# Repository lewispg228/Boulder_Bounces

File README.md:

# Boulder Bounces
The Museum of Boulder exhibit designers have paired with SparkFun to create Boulder Bounces: a mashup of Simon Says on trampolines. With sounds and spot lights triggering for every jump in the room, the exhibit is a bouncy blast for all ages.

Also includes slightly different code for the "Mighty Mini" and "Hop & Hear".

For a more in depth written post about the design choices, challenges, and future developments please visit the Enginursday blog post here:

https://www.sparkfun.com/news/2696

Visit this website for more info and links to all the products used in this project:

https://www.sparkfun.com/boulderbounces

To learn more about the Museum of Boulder and buy tickets please visit their website here:

https://www.museumofboulder.org

SparkFun products used in this project:

[Arduino Pro Mini 328 - 5V/16MHz](https://www.sparkfun.com/products/11113)

[Ultrasonic Sensor - HC-SR04](https://www.sparkfun.com/products/13959)

[Tsunami Super WAV Trigger](https://www.sparkfun.com/products/13810)

[SparkFun Beefcake Relay Control Kit Ver. 2.0](https://www.sparkfun.com/products/13815)

[SparkFun Music Instrument Shield](https://www.sparkfun.com/products/10587)

[7-Segment Display - 6.5" (Red)](https://www.sparkfun.com/products/8530)

[SparkFun Large Digit Driver](https://www.sparkfun.com/products/13279)

[SparkFun Noisy Cricket Stereo Amplifier - 1.5W](https://www.sparkfun.com/products/14475)

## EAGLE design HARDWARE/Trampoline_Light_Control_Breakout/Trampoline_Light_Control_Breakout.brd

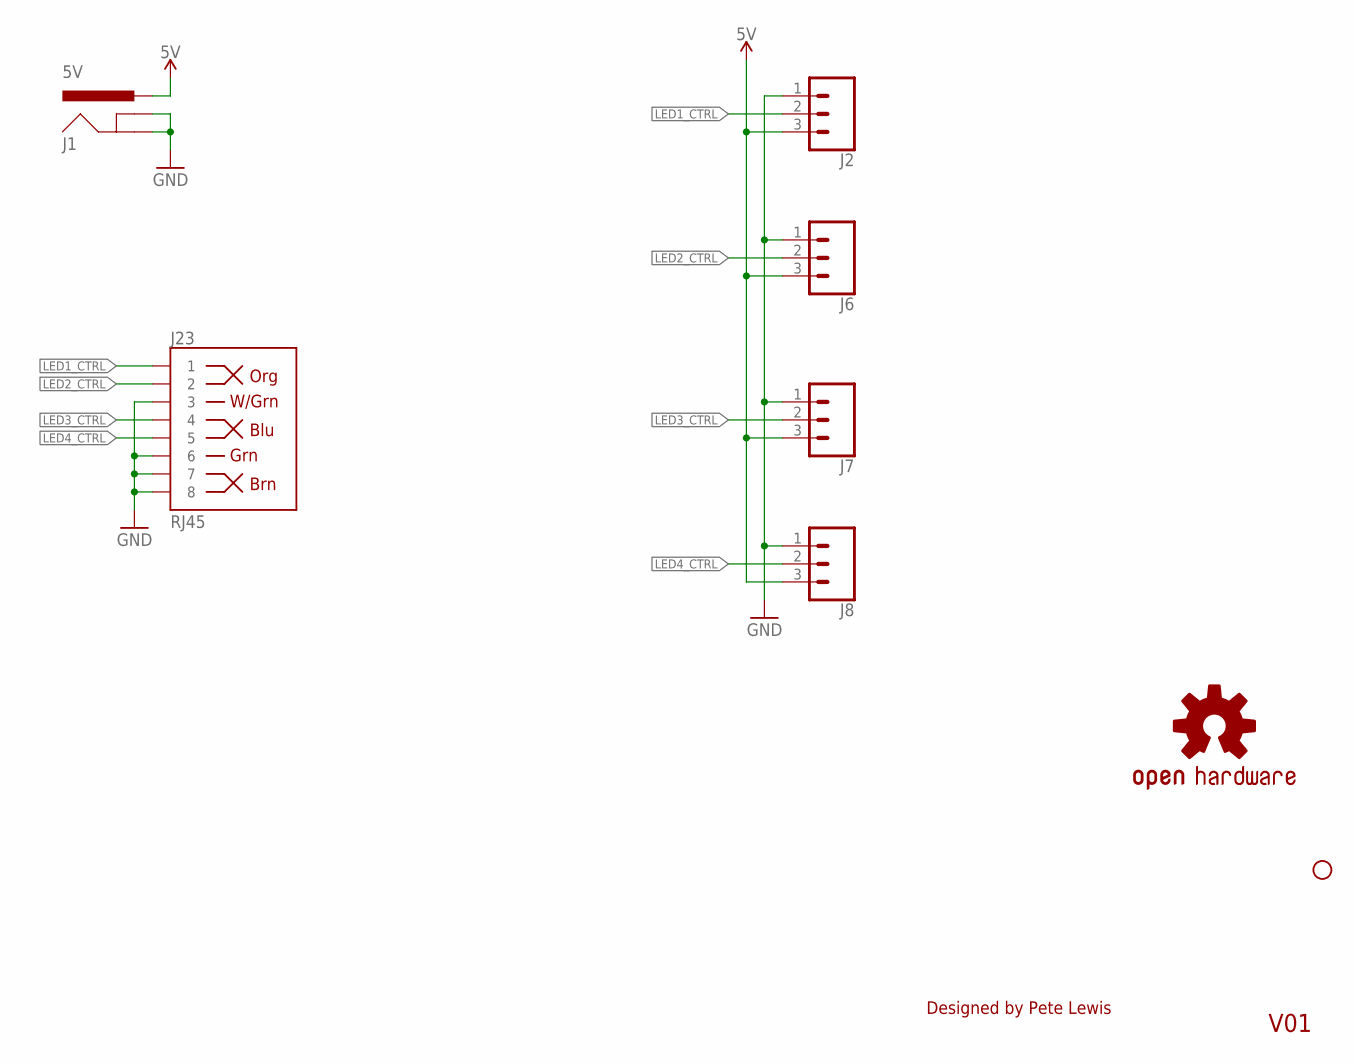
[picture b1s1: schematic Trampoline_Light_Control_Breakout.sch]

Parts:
J1: 5V; POWER_JACK_PTH_LOCK
J2, J6, J7, J8: CONN_03LONGPADS; 1X03_LONGPADS
J23: RJ45; RJ45-8
JP1: STAND-OFFTIGHTER; STAND-OFF-TIGHTER
LOGO2: OSHW-LOGOS; OSHW-LOGO-S

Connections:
GND: J1.GND, J1.GNDBREAK, J2.1, J6.1, J7.1, J8.1, J23.3, J23.6, J23.7, J23.8
LED1_CTRL: J2.2, J23.1
LED2_CTRL: J6.2, J23.2
LED3_CTRL: J7.2, J23.4
LED4_CTRL: J8.2, J23.5
VCC: J1.PWR, J2.3, J6.3, J7.3, J8.3

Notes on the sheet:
V01
Designed by Pete Lewis

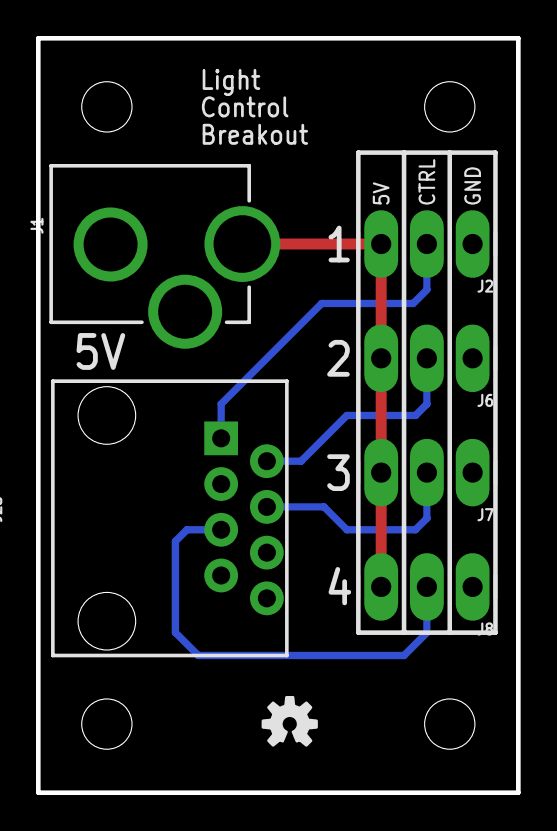
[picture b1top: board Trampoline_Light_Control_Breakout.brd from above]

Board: 2 copper layers, 26.7 x 41.9 mm, 11 parts (0 on the bottom side), 6 nets.

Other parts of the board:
JP2, JP3, JP7: STAND-OFFTIGHTER; STAND-OFF-TIGHTER

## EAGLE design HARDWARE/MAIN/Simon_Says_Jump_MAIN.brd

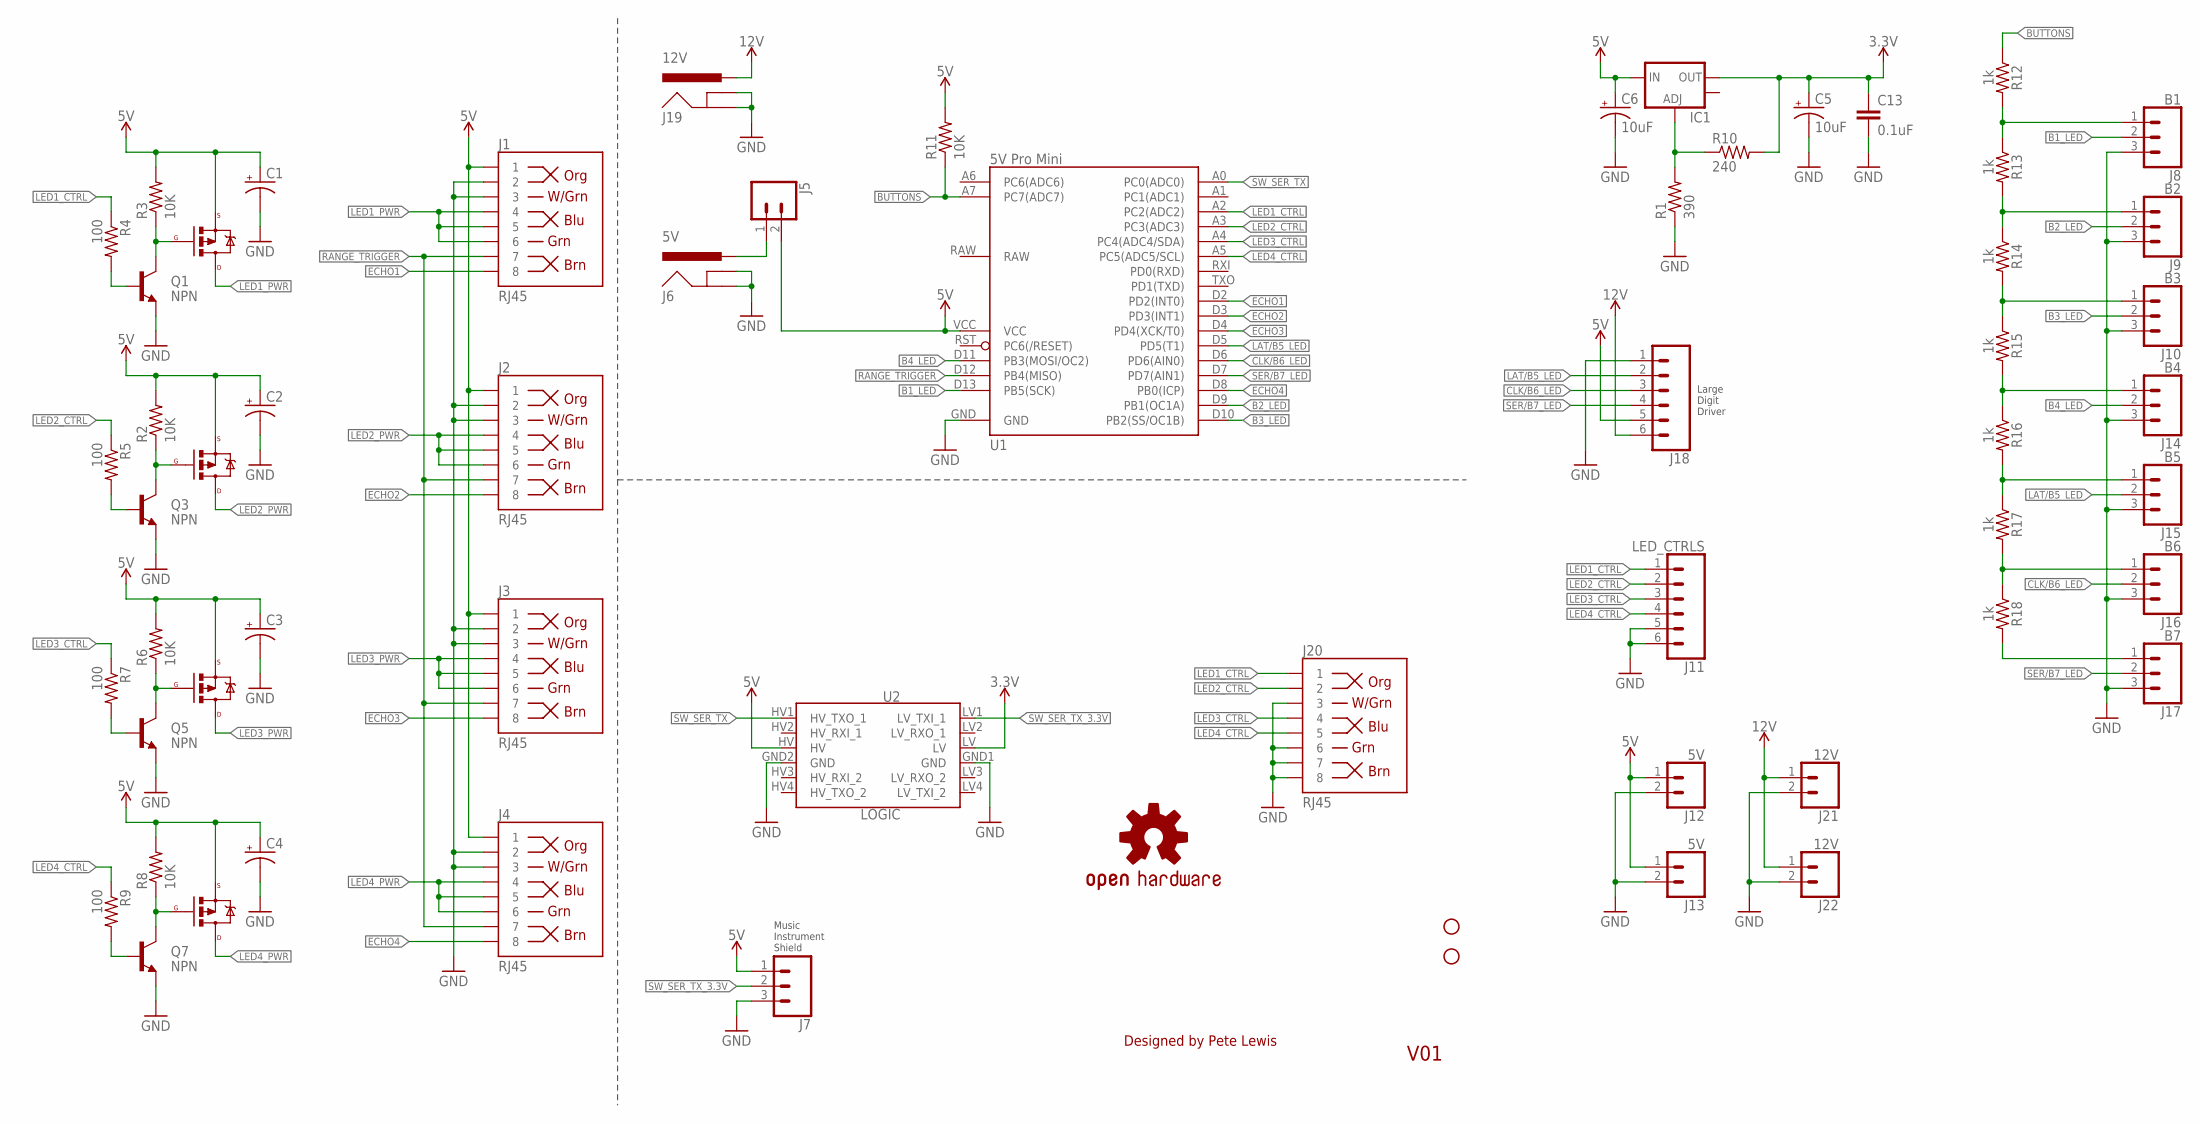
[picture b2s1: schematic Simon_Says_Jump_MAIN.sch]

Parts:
C1, C2, C3, C4: CAP_POLCPOL-RADIAL-10UF-25V-KIT; CPOL-RADIAL-10UF-25V-KIT
C5, C6: 10uF; EIA3216
C13: 0.1uF; 0603-CAP
IC1: V_REG_LM1117SOT223; SOT223
J1, J2, J3, J4, J20: RJ45; RJ45-8
J5: CONN_02PTH3; 1X02_LONGPADS
J6: 5V; POWER_JACK_PTH_LOCK
J7: CONN_03LONGPADS; 1X03_LONGPADS
J8: B1; 1X03_LONGPADS
J9: B2; 1X03_LONGPADS
J10: B3; 1X03_LONGPADS
J11: LED_CTRLS; 1X06_LONGPADS
J12, J13: 5V; 1X02_LONGPADS
J14: B4; 1X03_LONGPADS
J15: B5; 1X03_LONGPADS
J16: B6; 1X03_LONGPADS
J17: B7; 1X03_LONGPADS
J18: CONN_06LONGPADS; 1X06_LONGPADS
J19: 12V; POWER_JACK_PTH_LOCK
J21, J22: 12V; 1X02_LONGPADS
JP1, JP7: STAND-OFFTIGHTER; STAND-OFF-TIGHTER
LOGO1: OSHW-LOGOL; OSHW-LOGO-L
Q1, Q3, Q5, Q7: NPN; SOT23
Q2, Q4, Q6, Q8: P-Channel MOSFET; TO220V
R1: 390; 0603-RES
R2, R3, R6, R8, R11: 10K; 0603-RES
R4, R5, R7, R9: 100; 0603-RES
R10: 240; 0603-RES
R12, R13, R14, R15, R16, R17, R18: 1k; 0603
U1: 5V Pro Mini; ARDUINO_PRO_MINI-V13_DIP
U2: LOGIC; SPARKFUN_LOGIC_LEVEL_CONVERTER

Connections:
3.3V: C5.A (+), C13.1, IC1.2 (OUT), R10.2, U2.LV
5V: C1.1 (+), C2.1 (+), C3.1 (+), C4.1 (+), C6.A (+), IC1.3 (IN), J1.1, J2.1, J3.1, J4.1, J5.2, J7.1, J12.1, J13.1, J18.5, Q2.3 (S), Q4.3 (S), Q6.3 (S), Q8.3 (S), R2.2, R3.2, R6.2, R8.2, R11.2, U1.VCC, U2.HV
12V: J18.6, J19.PWR, J21.1, J22.1
B1_LED: J8.2, U1.D13 (PB5(SCK))
B2_LED: J9.2, U1.D9 (PB1(OC1A))
B3_LED: J10.2, U1.D10 (PB2(SS/OC1B))
B4_LED: J14.2, U1.D11 (PB3(MOSI/OC2))
BUTTONS: R11.1, R12.1, U1.A7 (PC7(ADC7))
CLK/B6_LED: J16.2, J18.3, U1.D6 (PD6(AIN0))
ECHO1: J1.8, U1.D2 (PD2(INT0))
ECHO2: J2.8, U1.D3 (PD3(INT1))
ECHO3: J3.8, U1.D4 (PD4(XCK/T0))
ECHO4: J4.8, U1.D8 (PB0(ICP))
GND: C1.2 (-), C2.2 (-), C3.2 (-), C4.2 (-), C5.C (-), C6.C (-), C13.2, J1.2, J1.3, J2.2, J2.3, J3.2, J3.3, J4.2, J4.3, J6.GND, J6.GNDBREAK, J7.3, J8.3, J9.3, J10.3, J11.5, J11.6, J12.2, J13.2, J14.3, J15.3, J16.3, J17.3, J18.1, J19.GND, J19.GNDBREAK, J20.3, J20.6, J20.7, J20.8, J21.2, J22.2, Q1.2 (E), Q3.2 (E), Q5.2 (E), Q7.2 (E), R1.1, U1.GND, U2.GND1 (GND), U2.GND2 (GND)
LAT/B5_LED: J15.2, J18.2, U1.D5 (PD5(T1))
LED1_CTRL: J11.1, J20.1, R4.1, U1.A2 (PC2(ADC2))
LED1_PWR: J1.4, J1.5, J1.6, Q2.2 (D)
LED2_CTRL: J11.2, J20.2, R5.1, U1.A3 (PC3(ADC3))
LED2_PWR: J2.4, J2.5, J2.6, Q4.2 (D)
LED3_CTRL: J11.3, J20.4, R7.1, U1.A4 (PC4(ADC4/SDA))
LED3_PWR: J3.4, J3.5, J3.6, Q6.2 (D)
LED4_CTRL: J11.4, J20.5, R9.1, U1.A5 (PC5(ADC5/SCL))
LED4_PWR: J4.4, J4.5, J4.6, Q8.2 (D)
unnamed: Q3.3 (C), Q4.1 (G), R2.1
unnamed: J8.1, R12.2, R13.1
unnamed: Q1.1 (B), R4.2
unnamed: J5.1, J6.PWR
unnamed: Q1.3 (C), Q2.1 (G), R3.1
unnamed: J9.1, R13.2, R14.1
unnamed: Q3.1 (B), R5.2
unnamed: Q5.3 (C), Q6.1 (G), R6.1
unnamed: Q5.1 (B), R7.2
unnamed: Q7.3 (C), Q8.1 (G), R8.1
unnamed: IC1.1 (ADJ), R1.2, R10.1
unnamed: Q7.1 (B), R9.2
unnamed: J10.1, R14.2, R15.1
unnamed: J14.1, R15.2, R16.1
unnamed: J15.1, R16.2, R17.1
unnamed: J16.1, R17.2, R18.1
unnamed: J17.1, R18.2
RANGE_TRIGGER: J1.7, J2.7, J3.7, J4.7, U1.D12 (PB4(MISO))
SER/B7_LED: J17.2, J18.4, U1.D7 (PD7(AIN1))
SW_SER_TX: U1.A0 (PC0(ADC0)), U2.HV1 (HV_TXO_1)
SW_SER_TX_3.3V: J7.2, U2.LV1 (LV_TXI_1)

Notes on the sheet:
V01
Designed by Pete Lewis
Music Instrument Shield
Large Digit Driver

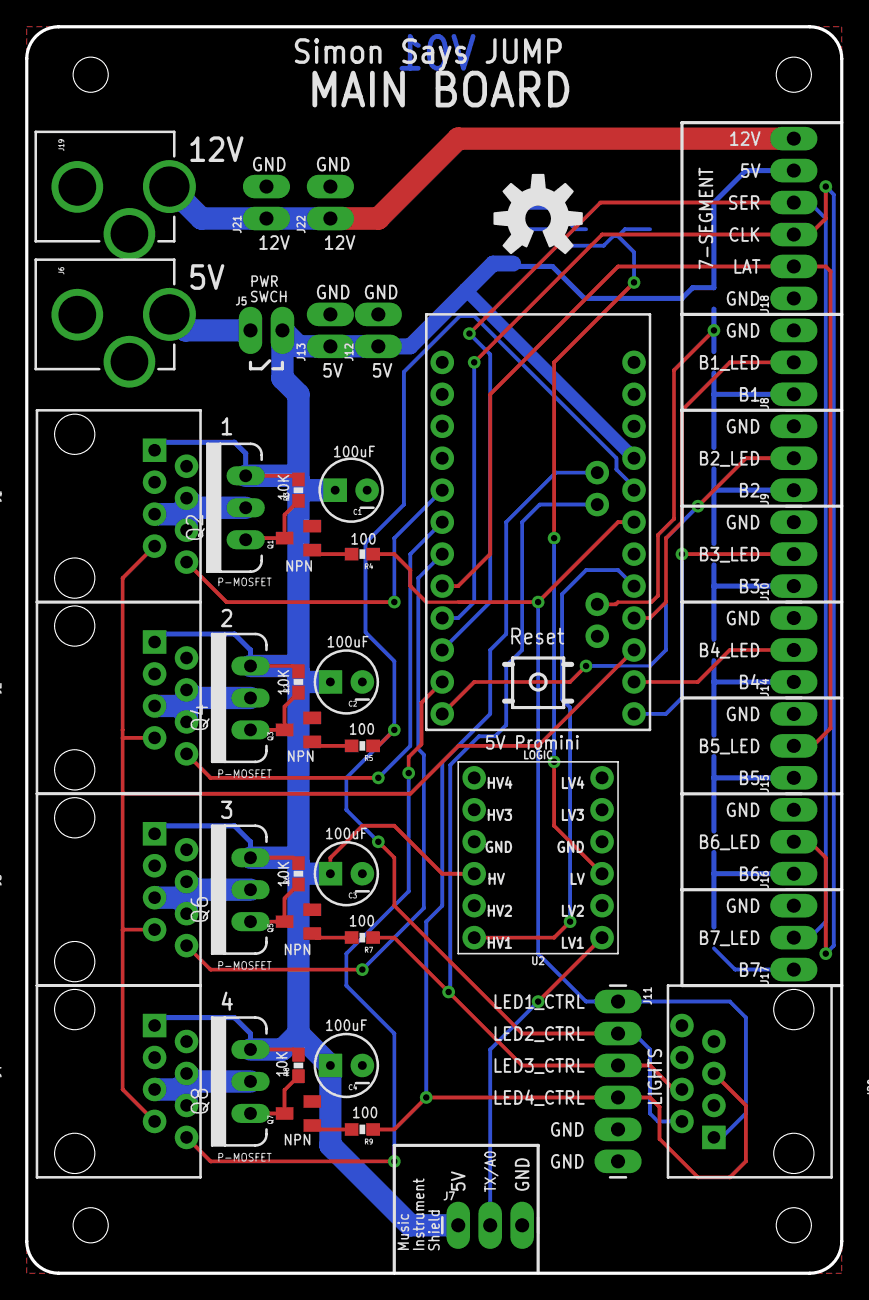
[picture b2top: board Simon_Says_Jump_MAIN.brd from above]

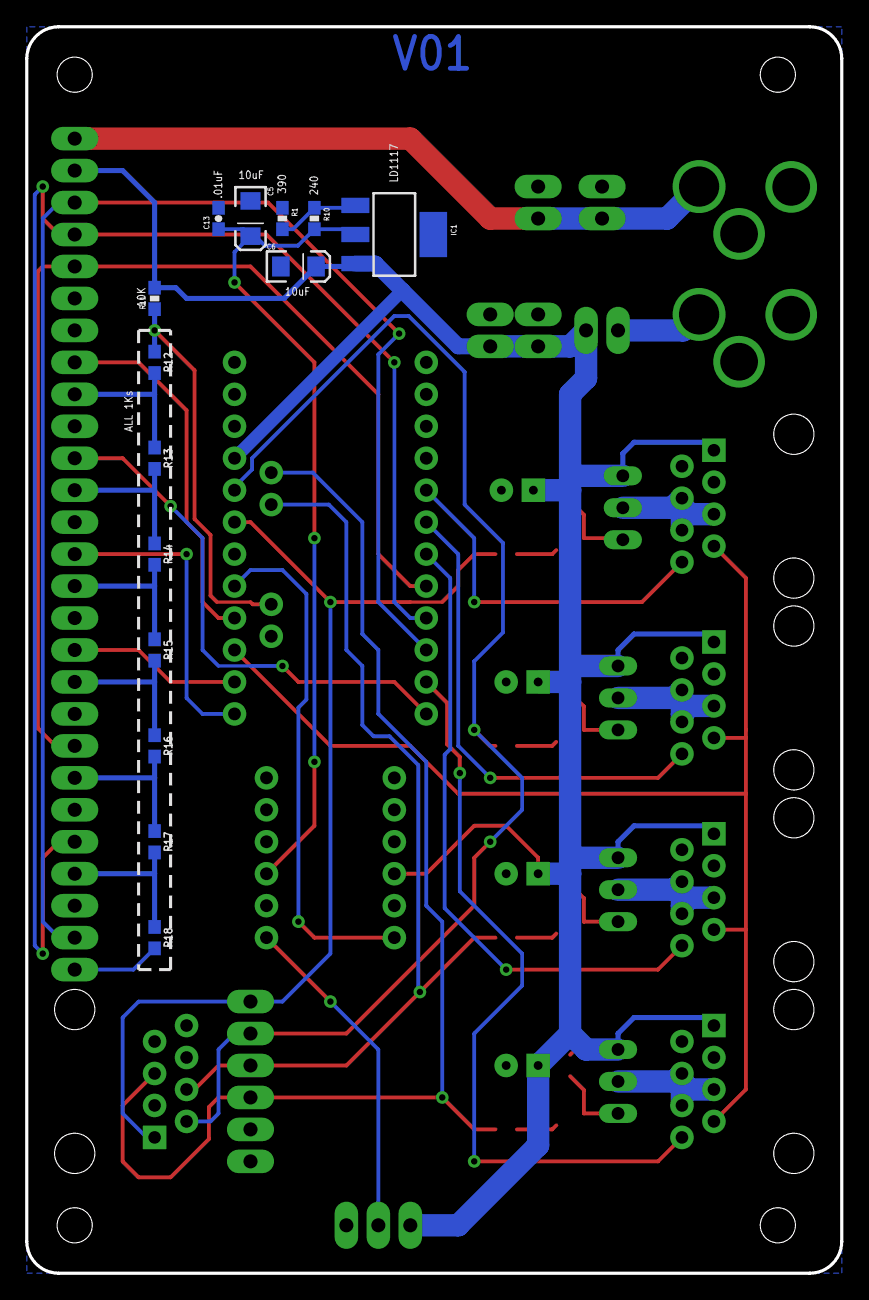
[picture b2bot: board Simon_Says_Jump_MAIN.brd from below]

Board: 2 copper layers, 64.8 x 99.1 mm, 63 parts (14 on the bottom side), 44 nets.

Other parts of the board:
JP2, JP3: STAND-OFFTIGHTER; STAND-OFF-TIGHTER

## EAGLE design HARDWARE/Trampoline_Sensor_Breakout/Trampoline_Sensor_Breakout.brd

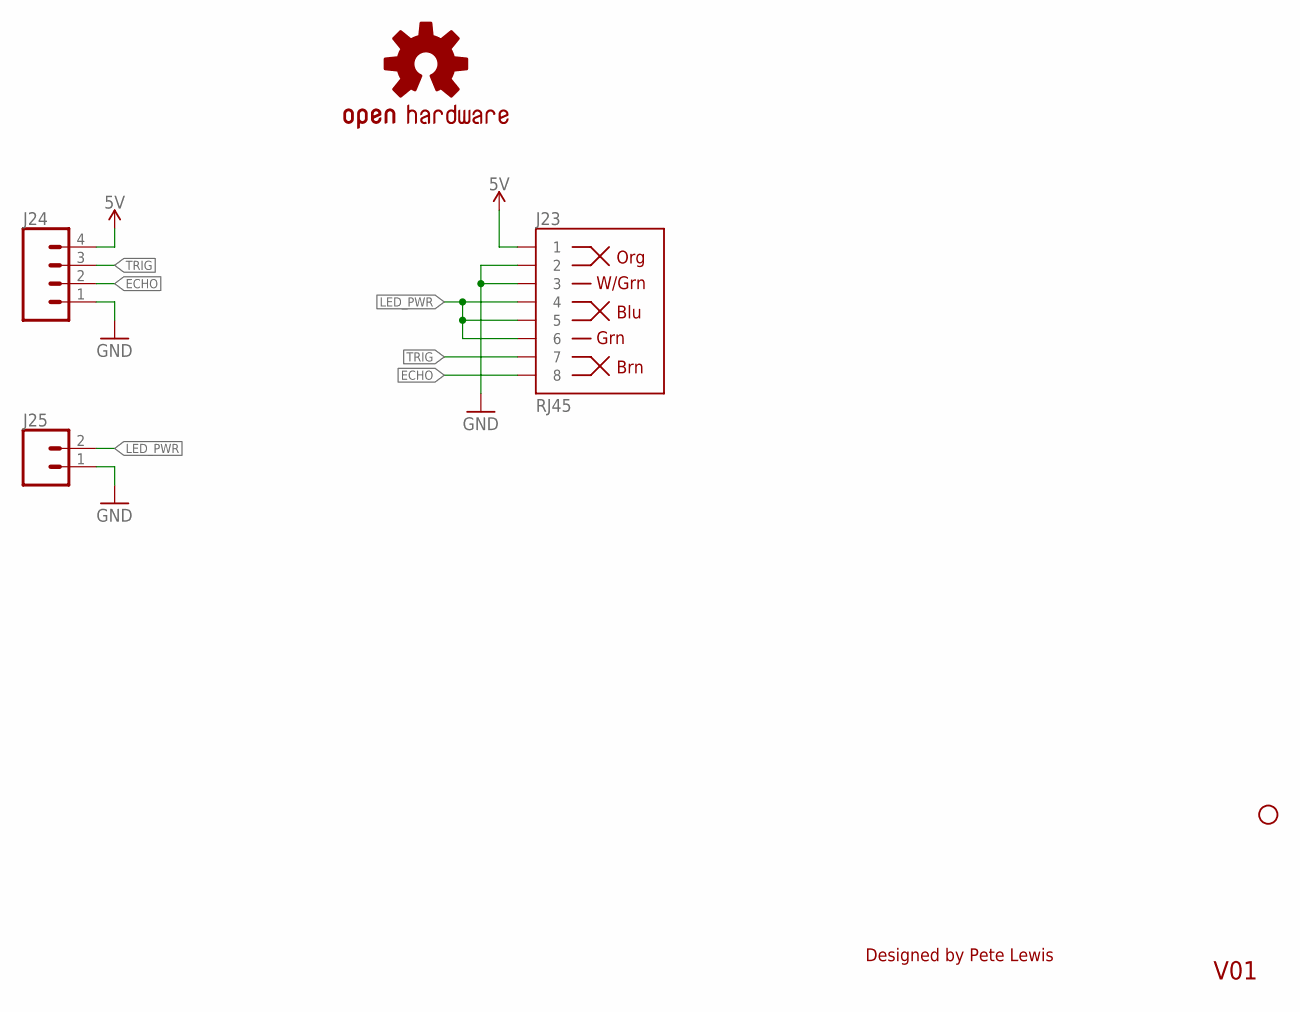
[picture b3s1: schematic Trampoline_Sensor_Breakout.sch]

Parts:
J23: RJ45; RJ45-8
J24: CONN_04LONGPADS; 1X04_LONGPADS
J25: CONN_02PTH3; 1X02_LONGPADS
JP8: STAND-OFFTIGHTER; STAND-OFF-TIGHTER
LOGO2: OSHW-LOGOS; OSHW-LOGO-S

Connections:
5V: J23.1, J24.4
ECHO: J23.8, J24.2
GND: J23.2, J23.3, J24.1, J25.1
LED_PWR: J23.4, J23.5, J23.6, J25.2
TRIG: J23.7, J24.3

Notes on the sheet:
V01
Designed by Pete Lewis

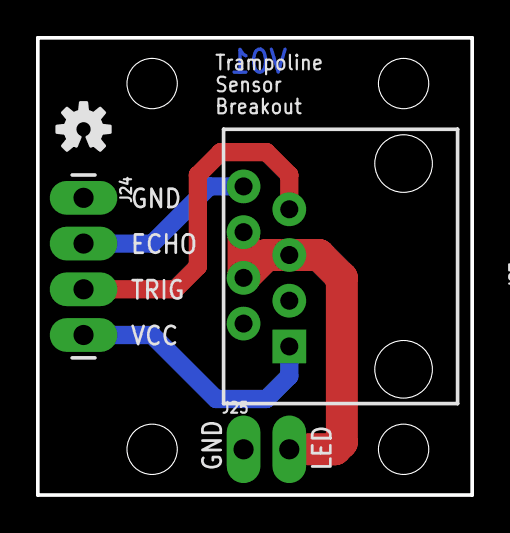
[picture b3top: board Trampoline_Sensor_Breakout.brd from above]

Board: 2 copper layers, 24.1 x 25.4 mm, 8 parts (0 on the bottom side), 5 nets.

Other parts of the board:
JP4, JP5, JP6: STAND-OFFTIGHTER; STAND-OFF-TIGHTER

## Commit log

2018-04-27 main board started
    includes:
    -RJ45 connectors to each trampoline
    -3pin header to connecto to music instrument shield
    -RFM69 breakout board for wirelessly talking to overhead lighting system
    -optional power switch header to potentially bring to toggle on a panel mount switch mounted elsewhere on the enclosure
    -high side switches for LED power control
2018-04-30 logic level converters for the range finders
    They need 5V Logic on trigger and echo pins.
    Also, they're gonna need power (durp), so I stole one of the GND lines in the ethernet connectors/cables to be a dedicated 5V (aka RAW) to power the range sensors.
2018-05-01 About to switch to 3 trampoline control
    Thought I'd do a commit here, because this could be a god fork point for the SFE installed 4-trampoline setup.
2018-05-02 Ready for layout
    Opted to keep 4 trampoline/led controls. I ended up using some of the LED control lines as also control lines to the 7-segment, because I won't need to use both of these at the same time.
    The toddler trampline is the only one that uses the 7-segment, and it will only use 2 buttons, so button 5,6,7 can be used for 7-segment.
    Also added in 12V barrel jack input for 7-segment.
    -added ethernet connector for control cable to overhead lights. These IO will control the beefcake relay boards that live up in the rafters with the can lights.
2018-05-02 routing in progress 30 airwires left
2018-05-02 more layout coming along
2018-05-03 Layout on main board complete
2018-05-03 Added in trampoline sensor breakout
    Each trampoline will need one of these. It has the 4-pin header to mate directly with the Ultrasonic Range Finders (Facing upward).
    Includes 4 standoffs for mounting to "arm" off of trampoline pole.
2018-05-03 moving main board into folder and renaming MAIN
2018-05-03 added light control breakout
    includes 5V barrel jack input and nice 3-pin headers for each beefcake relay connections
2018-05-03 gerbers
2018-05-04 started mini library with "board" packages for creating bases on lazer
2018-05-04 light controller breakout to mini library
2018-05-04 added light BASE ready for lazering
2018-05-04 Lights BASE - moved to BIG RED ENCLOSURE outer dimension
    This should now fit into the SparkFun big red enclosure box
    https://www.sparkfun.com/products/11366
2018-05-04 exp dxf for lazering
2018-05-04 MAIN BASE coming together
2018-05-10 Added noisy cricket to mini boards library for bases design work
2018-05-10 added noisey cricket to base
2018-05-11 Base_2 for those stations that need tsunamis
    also exported to dxf for lasering
2018-05-11 Bringing in current code from SFE trampoline installation
2018-05-11 midi reset on D7
2018-05-11 Bringing in some initial distance sensor testing code
2018-05-11 distance sensor testing tweaks
    Moved single range read to a function. Tried this out on all 4 ethernet ports and I'm getting good readings. Wahoo!
2018-05-11 wow so much stuff
2018-05-12 moved to array of distnaces and booleans tweeked threshold
2018-05-12 moved midi notes into checkButton_trampoline
    this allows for two or more trampolines to trigger at the same time.
    Also added a delay of 5 ms at start of distance read - this seemed to make all readings come back much better.
    locked in notes and bank to GM.
    still currently only messing around with musical instrument mode - need to work out buttons and mode switching
2018-05-14 Pulled return choice out of if statements
    moved it to the bottom, so it can still fire sounds on simultaneous jumps, and then return choice
2018-05-14 Got light control working, but still no gameplay
2018-05-14 free jump is working, and mode checking is working
2018-05-14 mode switching bug forgot to leave if statements
2018-05-14 moving to 3 trampoline setup
2018-05-14 added setLEDs() back into playback, also changed "maxed out" limits per trampoline
    it was stalling at 6 moves, because each one had already had 2, so I changed the "maxed out" limit to 3,3, and 2
2018-05-14 memory and free jump are working
    also mode button is swtiching correctly - avoiding loser sound if you select free jump in the middle of a memory game
2018-05-14 rafter board design
2018-05-14 tweaking button mode adc stuff
2018-05-14 trying to filter out bad readings on mode buttons
2018-05-14 pulled setMode code into check_mode_buttons
2018-05-14 newGameMelody moved to after attractmode in main loop
    this isthe proper place for this to indicate a new game has started
2018-05-15 cleared out a ton, wacka mole working although randomness could use some love
2018-05-15 all modes working
    strange that coming from wack to memory, it seems to immediately fail.
2018-05-15 wacks up to 20 for a win
2018-05-15 removed loser from wack-a-mole, also removed checkButton from old non-trampoline checking
2018-05-15 global timeout in wack a mole is working
2018-05-15 wack a mole stays in mode unless global static timeout occurs
2018-05-15 memory now has global timeout to free jump
    it will repeat memory round until global timeout happens.
    note, it's a little longer than GLOBAL_STATIC_TIMEOUT_LIMIT because, it needs to fail a memory game to eventually check that global static timeout. This is okay, it just means that you need to let it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
2018-05-15 fixed strange wack-a-mole quick looping bug
    I was getting stuck in the while loop in wack a mole, even if check_mode_button was changing MODE. This needed a mode check to also break out of this while loop.
2018-05-15 saved as hop and hear - starting code for little two trampolines
2018-05-15 hop and hear thresh
    "high" reading on trampoline is reading pretty solid at 1130ish
2018-05-15 wav files pulled in
    some of them wouldn't open... may need to find other sources (farm had some, and elephant wouldn' open. could have been others too)
2018-05-16 made MP3 versions via itunes
    renamed for qwicc mp3 file format "F001.mp3"
    Also, fixed meadowlark, the original WAV was 41 seconds - whoops.
2018-05-17 test tracks and ini file seems to be working
2018-05-17 hop and hear cleared out a ton and working
2018-05-17 saving hop and hear as mighty mini
2018-05-17 tsunami latest firmware im using just to have in case
2018-05-17 re-naming Tsunami firmware file for bootload (v108)
2018-05-17 mighty mini working
    still need to incorporate mode LEDs, but everything else is working: counts, mode switching, global timeouts, display clearing.
2018-05-18 mode LEDs in simon says working
2018-05-18 mode leds in mighty mini working
2018-05-18 added button led to hop and hear - working
    tweaked button 6 value, it wasn't catching a button press cause it's coming in more like 390
2018-05-18 wav files snipping and better cartoon sounds brought in
2018-05-18 mighty mini added drum tracks
    drum tracks start at 60.
    also, duck tracks are 8 total now.
    tested this, it's working
2018-05-18 playable tracks are 70 - 77, so add zero or 7
    random does not include the upper limit. so I say there are 8 tracsk in defines, and I only want to go from 70 to 77.
2018-05-18 some colorado tracks more to come in a bit
2018-05-18 all of colorado done 7 tracks total 80-86
2018-05-18 colorado tracks start at 80 and there are 7 of them
2018-05-19 added window tolerance variable to buttons now it's 10, was 5 before
2018-05-19 threshold to catch G and lighter jumpers
    pretty good readings at 1660, so 1500 is safe
2018-05-25 updated name to match repo
2018-05-30 readme cleanup and links
    this is mostly the same stuff that's in the youtube video description, but thought it'd be useful here as well.
2018-05-30 markdown links on products
2018-07-11 fixed "stall out" in add_to_moves()
    -My while(1) loop that keeps calling random until it meets the sequence rules was stalling out sometimes. I changed it to always break out of the while(1) by using an on_deck_buttons array that is ad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
    -added more debug about gameboard, add_to_moves logic and more
    -attempted to require the first three buttons in gameBoard to be unique, but it doesn't seem to be working with the few times I tested it. I had a couple repeats.
    -added clear_gameBoard() to more easily watch debug when you play more rounds. zeroing them all out, shows
2018-07-11 testing sequence generation
    keeping it random but within rules is tough. I decided to stray away from the add_to_moves approach, and go with generating an entire sequence in an array all at once. This way I could get very speci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
    I still need to bake this into my main simon trampolines sketch, but at least this example sketch is working like I like it for now in a serial terminal.
2018-07-11 added function for pre-set gameBoards - may not use
    may not use this at all, but started it, so I thought I'd commit it in.
2019-07-16 Adjusting filter to remove other error readings
    After installing the trampolines at SparkFun, there was an occasional reading of 16 that was falsely triggering wrong trampolines. Changed the filter to ignore any readings bleow 50.

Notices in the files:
parts and their libraries:
SparkFun-Connectors: Licensing: Creative Commons ShareAlike 4.0 International - https://creativecommons.org/licenses/by-sa/4.0
